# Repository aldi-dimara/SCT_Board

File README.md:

# SCT_Board

This board is used to monitor current using SCT-013-020 with maxium current of 20A. The main process is conducted by NodeMCU v1.0.

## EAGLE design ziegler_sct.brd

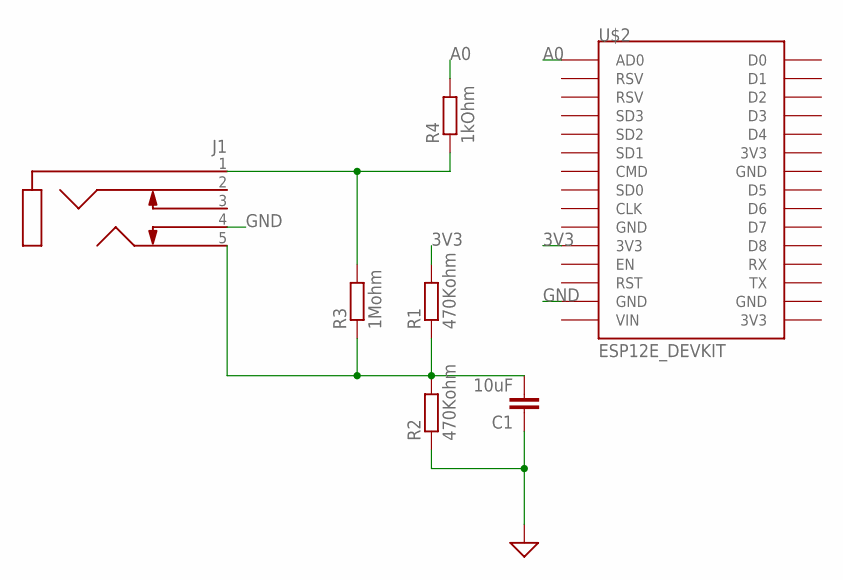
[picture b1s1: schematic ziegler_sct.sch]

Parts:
C1: 10uF; C5B3
J1: STEREO_JACK3F07; 3.5AUDIO_3F07
R1, R2: 470Kohm; 0204/7
R3: 1Mohm; 0204/7
R4: 1kOhm; 0204/7
U$2: ESP12E_DEVKIT

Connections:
3V3: R1.2, U$2.3V3@0 (3V3)
A0: R4.2, U$2.AD0
GND: C1.1, J1.4 (RSWITCH), R2.1, U$2.GND@1 (GND)
unnamed: C1.2, J1.5 (RING), R1.1, R2.2, R3.1
unnamed: J1.1 (SLEEVE), R3.2, R4.1

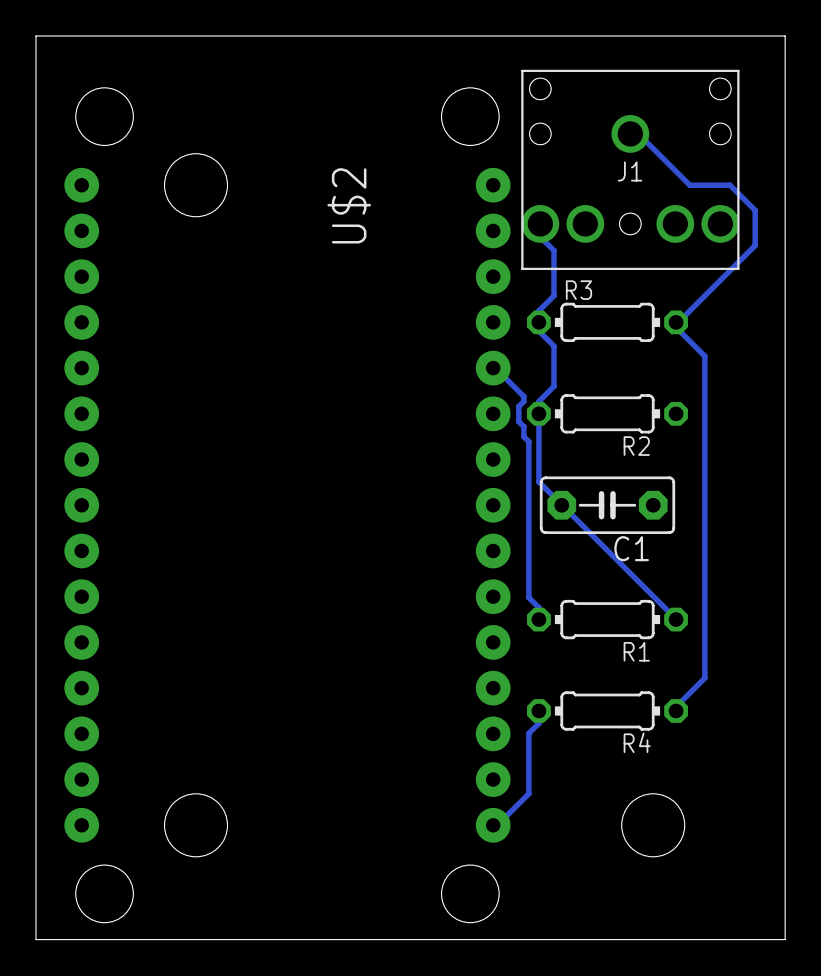
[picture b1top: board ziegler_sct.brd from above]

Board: 2 copper layers, 41.6 x 50.2 mm, 7 parts (0 on the bottom side), 5 nets.
